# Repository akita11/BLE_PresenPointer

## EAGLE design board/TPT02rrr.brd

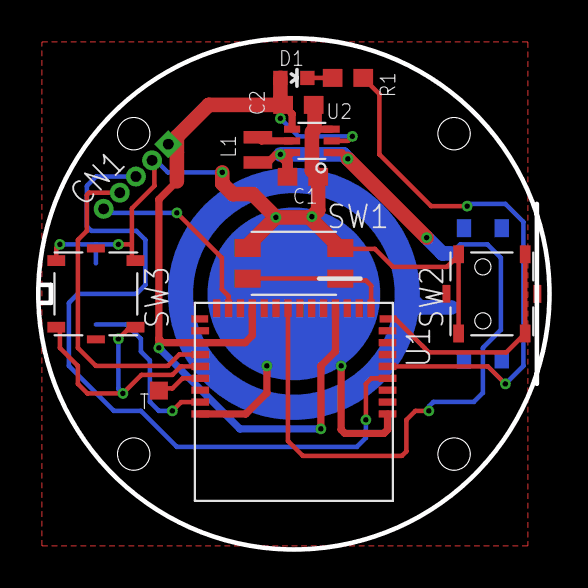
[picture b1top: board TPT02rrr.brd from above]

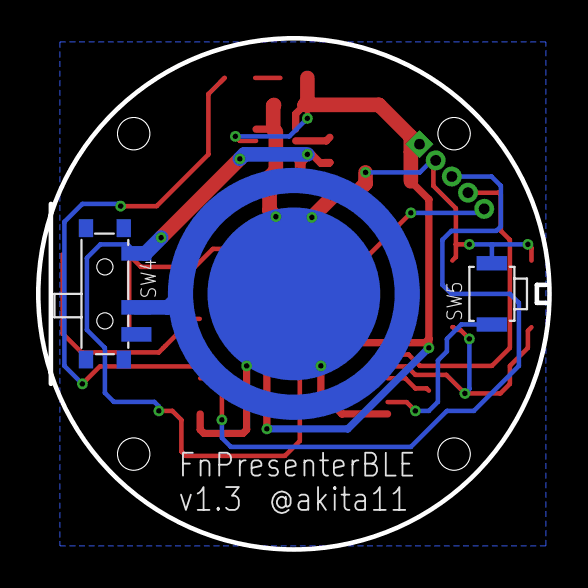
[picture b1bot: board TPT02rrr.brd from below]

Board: 2 copper layers, 28.4 x 28.4 mm, 16 parts (4 on the bottom side), 15 nets.

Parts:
C1, C2: 10u; 0603
CN1: 1X5_50MIL
CNM, CNM1: CON_P01SMD1MM; PAD_SMD1MM
CNP: CON_P01SMD1MM; PAD_SMD1MM
D1: SPARKFUN_LED-0603
L1: INDUCTORSMD2016; 2016
R1: 10k; 0603
SW1: SW_EVQP2
SW2, SW3: SW_EVQPLBA08
SW4: SW_SLIDECUS12B; SW_CUS-12B
SW5: SW_B3U-3000P
U1: MOD_CYBLE014008-00
U2: REG_TPS61221; SC70-6

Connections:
+3V3: C2.1, CN1.P$1, D1.A, U1.P$7, U1.P$13, U1.P$20, U2.P$2, U2.P$4
GND: C1.2, C2.2, CN1.P$2, CNM.P$1, SW1.PB1, SW1.PB2, SW2.B1, SW2.B2, SW3.B1, SW3.B2, SW5.P$2, U1.P$1, U1.P$32, U2.P$3
LED_A: R1.1, U1.P$28
unnamed: L1.P$2, U2.P$5
unnamed: D1.C, R1.2
unnamed: CNP.P$1, SW4.P$2
SWB: SW2.A1, SW2.A2, U1.P$24
SWDCLK: CN1.P$4, U1.P$6
SWDIO: CN1.P$5, U1.P$11
SWI: SW5.P$1, U1.P$2
SWM: SW1.PA1, SW1.PA2, U1.P$23
SWO: SW3.A1, SW3.A2, U1.P$5
TXD: CNM1.P$1, U1.P$4
VBAT: C1.1, L1.P$1, SW4.P$1, U1.P$16, U2.P$1, U2.P$6
XRES: CN1.P$3, U1.P$29
